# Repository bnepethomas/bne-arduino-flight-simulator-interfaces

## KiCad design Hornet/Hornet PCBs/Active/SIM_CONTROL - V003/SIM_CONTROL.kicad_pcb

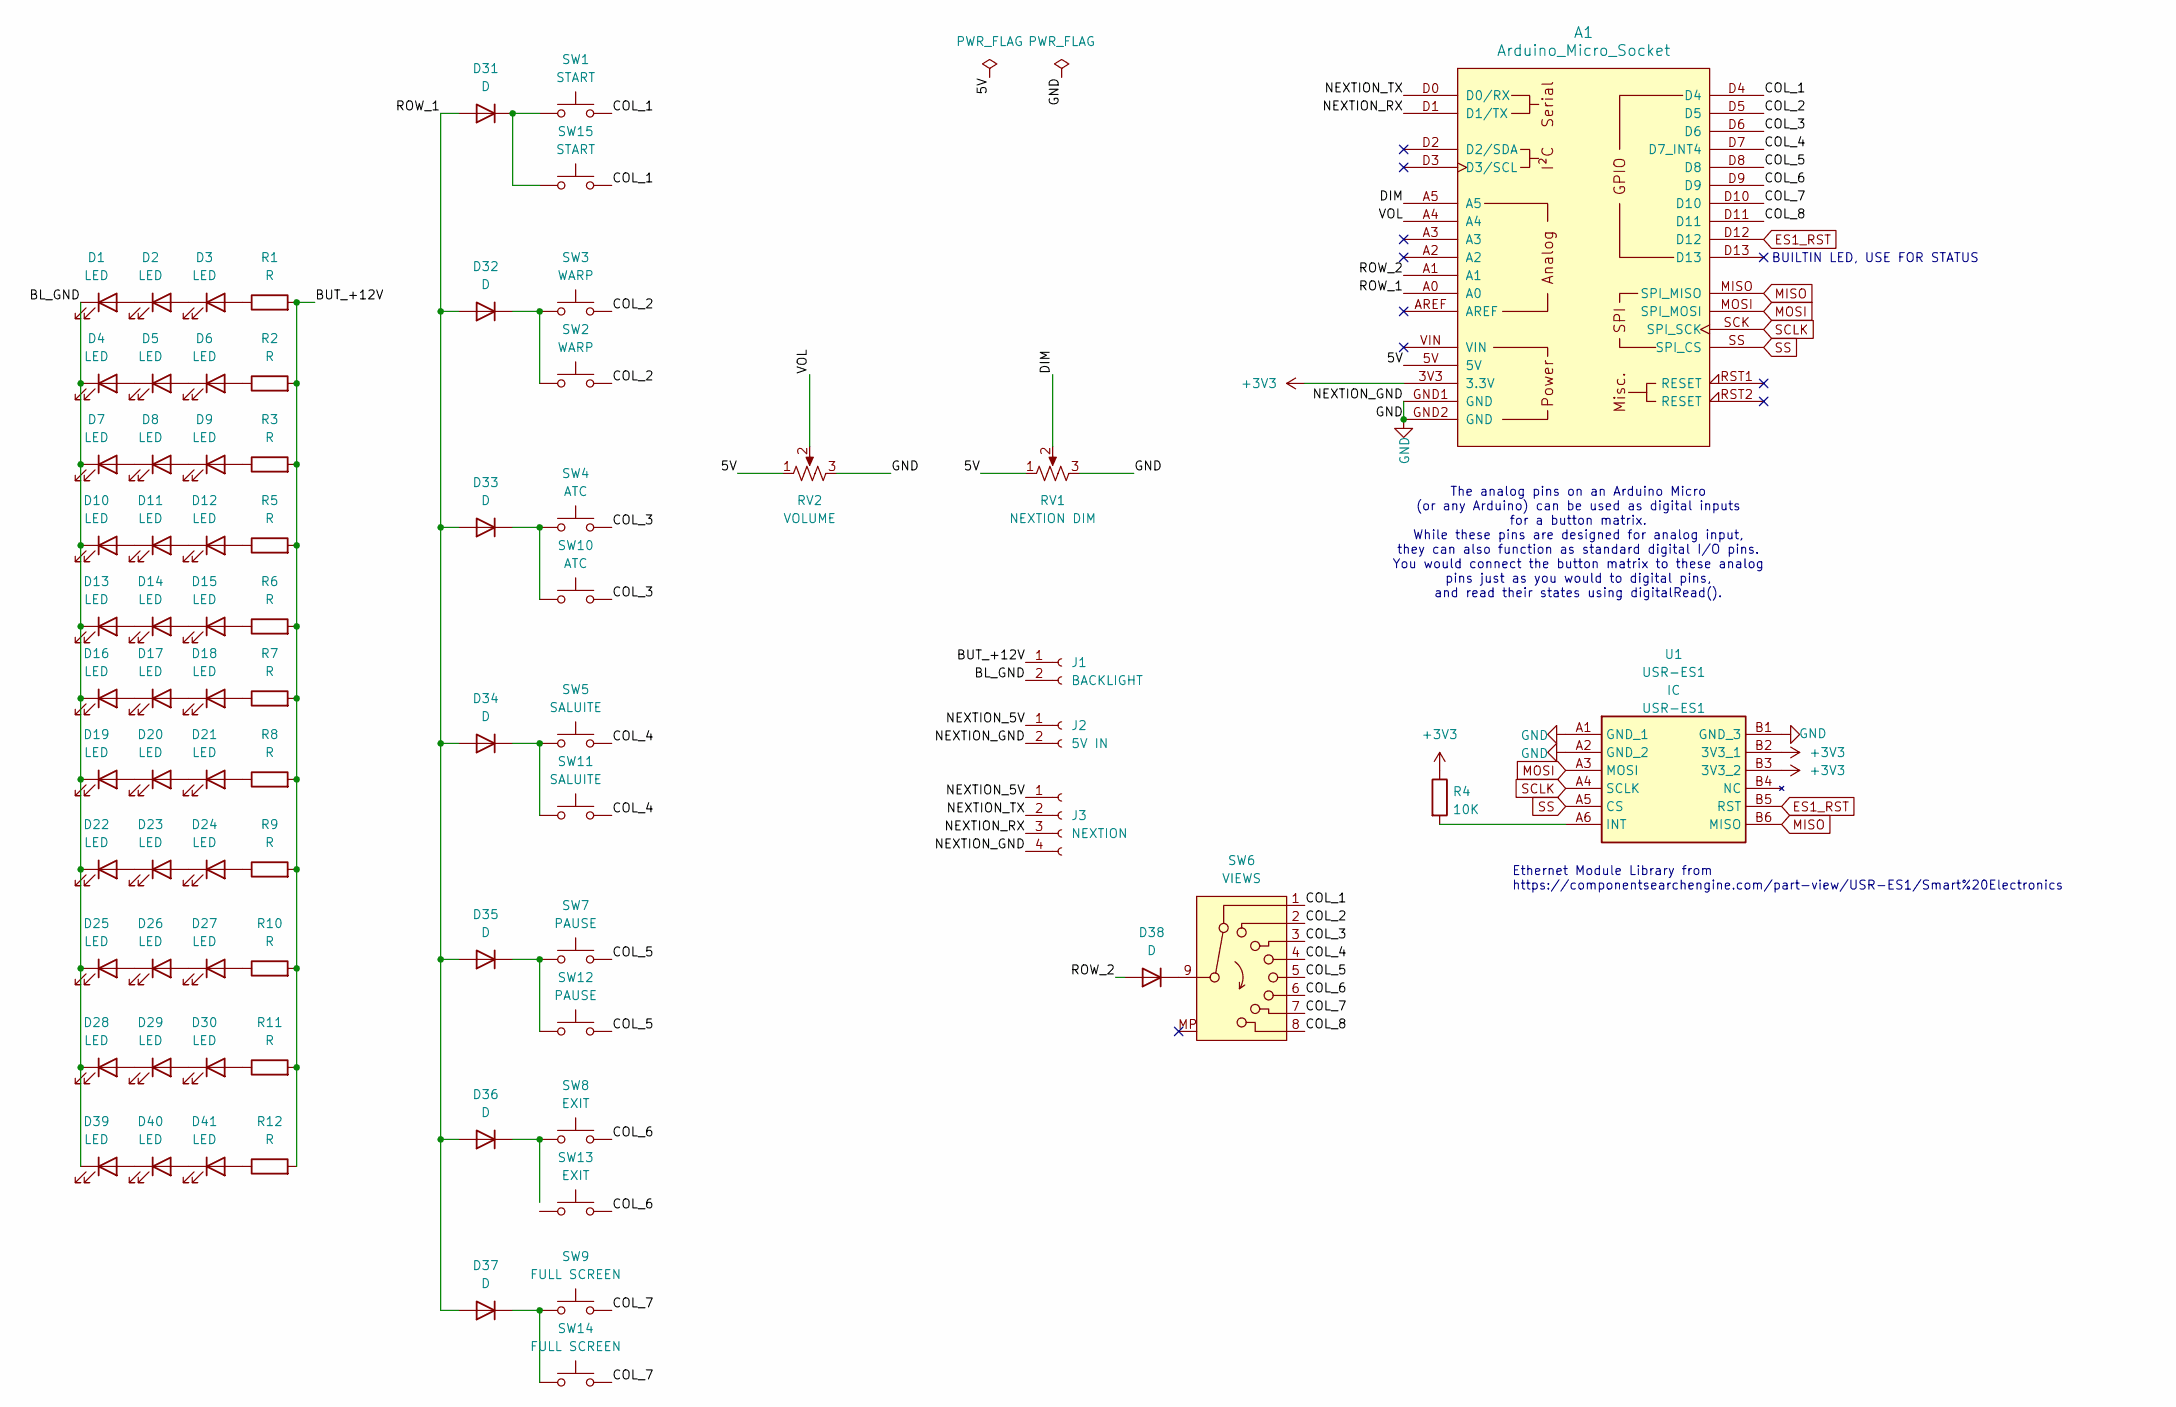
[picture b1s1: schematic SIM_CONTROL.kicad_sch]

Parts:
A1: Arduino_Micro_Socket
D1, D2, D3, D4, D5, D6, D7, D8, D9, D10, D11, D12, D13, D14, D15, D16, D17, D18, D19, D20, D21, D22, D23, D24, D25, D26, D27, D28, D29, D30, D39, D40, D41: LED; LED_0805_2012Metric
D31, D32, D33, D34, D35, D36, D37, D38: D; D_0805_2012Metric_Pad1.15x1.40mm_HandSolder
J1: BACKLIGHT; Molex_KK-254_AE-6410-02A_1x02_P2.54mm_Vertical
J2: 5V IN; BarrelJack_Horizontal
J3: NEXTION; Molex_KK-254_AE-6410-04A_1x04_P2.54mm_Vertical
R1, R2, R3, R5, R6, R7, R8, R9, R10, R11, R12: R; R_0805_2012Metric
R4: 10K; R_0805_2012Metric
RV1: NEXTION DIM; JST_XA_B03B-XASK-1_1x03_P2.50mm_Vertical
RV2: VOLUME; JST_XA_B03B-XASK-1_1x03_P2.50mm_Vertical
SW1, SW15: START; SW_Push_1P1T_XKB_TS-1187A
SW2, SW3: WARP; SW_Push_1P1T_XKB_TS-1187A
SW4, SW10: ATC; SW_Push_1P1T_XKB_TS-1187A
SW5, SW11: SALUITE; SW_Push_1P1T_XKB_TS-1187A
SW6: VIEWS; Molex_KK-254_AE-6410-10A_1x10_P2.54mm_Vertical
SW7, SW12: PAUSE; SW_Push_1P1T_XKB_TS-1187A
SW8, SW13: EXIT; SW_Push_1P1T_XKB_TS-1187A
SW9, SW14: FULL SCREEN; SW_Push_1P1T_XKB_TS-1187A
U1: USR-ES1; USRES1; Manufacturer_Part_Number USR-ES1

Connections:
+3V3: A1.3V3 (3.3V), R4.1, U1.B2 (3V3_1), U1.B3 (3V3_2)
/5V: A1.5V, RV1.1, RV2.1
/BL_GND: D1.1 (K), D4.1 (K), D7.1 (K), D10.1 (K), D13.1 (K), D16.1 (K), D19.1 (K), D22.1 (K), D25.1 (K), D28.1 (K), D39.1 (K), J1.2
/BUT_+12V: J1.1, R1.2, R2.2, R3.2, R5.2, R6.2, R7.2, R8.2, R9.2, R10.2, R11.2, R12.2
/COL_1: A1.D4, SW1.2, SW6.1, SW15.2
/COL_2: A1.D5, SW2.2, SW3.2, SW6.2
/COL_3: A1.D6, SW4.2, SW6.3, SW10.2
/COL_4: A1.D7 (D7_INT4), SW5.2, SW6.4, SW11.2
/COL_5: A1.D8, SW6.5, SW7.2, SW12.2
/COL_6: A1.D9, SW6.6, SW8.2, SW13.2
/COL_7: A1.D10, SW6.7, SW9.2, SW14.2
/COL_8: A1.D11, SW6.8
/DIM: A1.A5, RV1.2
/NEXTION_5V: J2.1, J3.1
/NEXTION_RX: A1.D1 (D1/TX), J3.3
/NEXTION_TX: A1.D0 (D0/RX), J3.2
/ROW_1: A1.A0, D31.2 (A), D32.2 (A), D33.2 (A), D34.2 (A), D35.2 (A), D36.2 (A), D37.2 (A)
/ROW_2: A1.A1, D38.2 (A)
/VOL: A1.A4, RV2.2
ES1_RST: A1.D12, U1.B5 (RST)
GND: A1.GND1 (GND), A1.GND2 (GND), J2.2, J3.4, RV1.3, RV2.3, U1.A1 (GND_1), U1.A2 (GND_2), U1.B1 (GND_3)
MISO: A1.MISO (SPI_MISO), U1.B6 (MISO)
MOSI: A1.MOSI (SPI_MOSI), U1.A3 (MOSI)
unnamed: D1.2 (A), D2.1 (K)
unnamed: D2.2 (A), D3.1 (K)
unnamed: D3.2 (A), R1.1
unnamed: D4.2 (A), D5.1 (K)
unnamed: D5.2 (A), D6.1 (K)
unnamed: D6.2 (A), R2.1
unnamed: D7.2 (A), D8.1 (K)
unnamed: D8.2 (A), D9.1 (K)
unnamed: D9.2 (A), R3.1
unnamed: D10.2 (A), D11.1 (K)
unnamed: D11.2 (A), D12.1 (K)
unnamed: D12.2 (A), R5.1
unnamed: D13.2 (A), D14.1 (K)
unnamed: D14.2 (A), D15.1 (K)
unnamed: D15.2 (A), R6.1
unnamed: D16.2 (A), D17.1 (K)
unnamed: D17.2 (A), D18.1 (K)
unnamed: D18.2 (A), R7.1
unnamed: D19.2 (A), D20.1 (K)
unnamed: D20.2 (A), D21.1 (K)
unnamed: D21.2 (A), R8.1
unnamed: D22.2 (A), D23.1 (K)
unnamed: D23.2 (A), D24.1 (K)
unnamed: D24.2 (A), R9.1
unnamed: D25.2 (A), D26.1 (K)
unnamed: D26.2 (A), D27.1 (K)
unnamed: D27.2 (A), R10.1
unnamed: D28.2 (A), D29.1 (K)
unnamed: D29.2 (A), D30.1 (K)
unnamed: D30.2 (A), R11.1
unnamed: D31.1 (K), SW1.1, SW15.1
unnamed: D32.1 (K), SW2.1, SW3.1
unnamed: D33.1 (K), SW4.1, SW10.1
unnamed: D34.1 (K), SW5.1, SW11.1
unnamed: D35.1 (K), SW7.1, SW12.1
unnamed: D36.1 (K), SW8.1
unnamed: D37.1 (K), SW9.1, SW14.1
unnamed: D38.1 (K), SW6.9
unnamed: D39.2 (A), D40.1 (K)
unnamed: D40.2 (A), D41.1 (K)
unnamed: D41.2 (A), R12.1
unnamed: R4.2, U1.A6 (INT)
SCLK: A1.SCK (SPI_SCK), U1.A4 (SCLK)
SS: A1.SS (SPI_CS), U1.A5 (CS)

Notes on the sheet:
Ethernet Module Library from https://componentsearchengine.com/part-view/USR-ES1/Smart%20Electronics
The analog pins on an Arduino Micro (or any Arduino) can be used as digital inputs for a button matrix. While these pins are designed for analog input, they can also function as standard digital I/O pins. You would connect the button matrix to these analog pins just as you would to digital pins, an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
BUILTIN LED, USE FOR STATUS

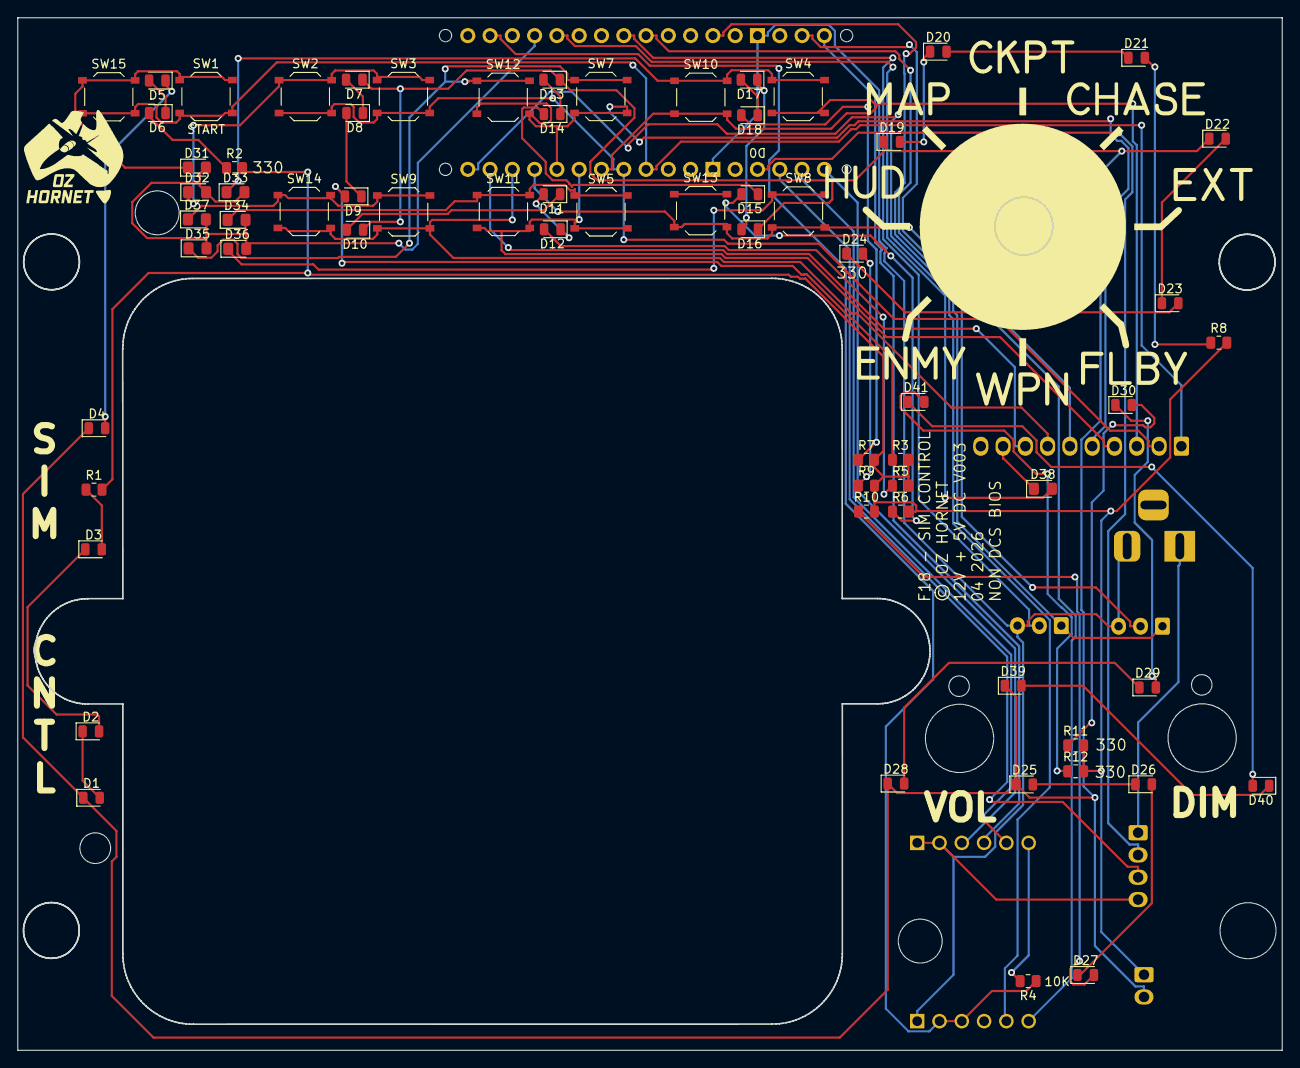
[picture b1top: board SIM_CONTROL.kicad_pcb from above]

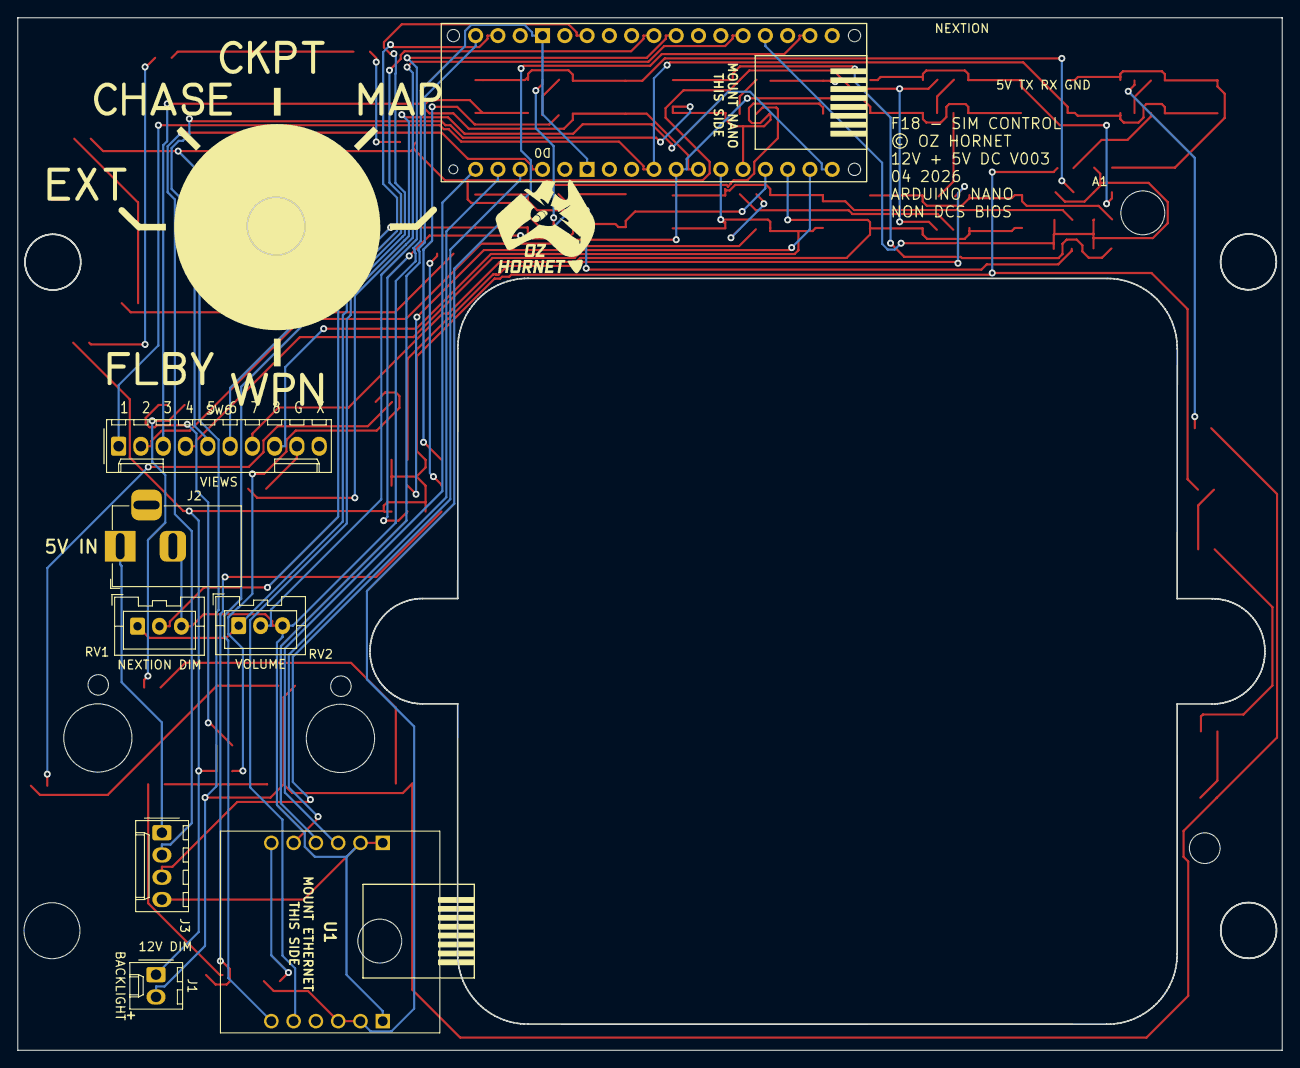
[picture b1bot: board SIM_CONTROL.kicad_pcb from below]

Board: 2 copper layers, 144.1 x 117.7 mm, 76 parts (8 on the bottom side), 67 nets.

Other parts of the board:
MH12: Switch_Rotary_8pos45Deg; A12505RNZQ - SWITCH, ROTARY, 45 DEG, 8-POS

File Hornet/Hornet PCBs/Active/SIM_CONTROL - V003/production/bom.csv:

Designator,Footprint,Quantity,Value,LCSC Part #
A1,Arduino_Micro_Socket,1,Arduino_Micro_Socket,
"D1, D10, D11, D12, D13, D14, D15, D16, D17, D18, D19, D2, D20, D21, D22, D23, D24, D25, D26, D27, D28, D29, D3, D30, D39, D4, D40, D41, D5, D6, D7, D8, D9",0805,33,LED,
"D31, D32, D33, D34, D35, D36, D37, D38",0805,8,D,
J1,Molex_KK-254_AE-6410-02A_1x02_P2.54mm_Vertical,1,BACKLIGHT,
J2,BarrelJack_Horizontal,1,5V IN,
J3,Molex_KK-254_AE-6410-04A_1x04_P2.54mm_Vertical,1,NEXTION,
"R1, R10, R11, R12, R2, R3, R5, R6, R7, R8, R9",0805,11,R,
R4,0805,1,10K,
RV1,JST_XA_B03B-XASK-1_1x03_P2.50mm_Vertical,1,NEXTION DIM,
RV2,JST_XA_B03B-XASK-1_1x03_P2.50mm_Vertical,1,VOLUME,
"SW1, SW15",SW_Push_1P1T_XKB_TS-1187A,2,START,
"SW10, SW4",SW_Push_1P1T_XKB_TS-1187A,2,ATC,
"SW11, SW5",SW_Push_1P1T_XKB_TS-1187A,2,SALUITE,
"SW12, SW7",SW_Push_1P1T_XKB_TS-1187A,2,PAUSE,
"SW13, SW8",SW_Push_1P1T_XKB_TS-1187A,2,EXIT,
"SW14, SW9",SW_Push_1P1T_XKB_TS-1187A,2,FULL SCREEN,
"SW2, SW3",SW_Push_1P1T_XKB_TS-1187A,2,WARP,
SW6,Molex_KK-254_AE-6410-10A_1x10_P2.54mm_Vertical,1,VIEWS,
U1,USRES1,1,USR-ES1,

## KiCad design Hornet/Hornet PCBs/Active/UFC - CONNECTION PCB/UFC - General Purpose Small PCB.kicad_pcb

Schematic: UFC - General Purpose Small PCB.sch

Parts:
D1: LED; LED_D5.0mm
H1, H2, H3, H4, H5, H6, H7, H8, H9: MountingHole; MountingHole_3.2mm_M3
J1: AP COL IN; Molex_1x03_P2.54mm_Vertical
J2: AP ROW IN; Molex_1x03_P2.54mm_Vertical
J3: AP COL OUT; Molex_1x03_P2.54mm_Vertical
J4: AP ROW OUT; Molex_1x03_P2.54mm_Vertical
J5: UFC LED COL IN; Molex_1x03_P2.54mm_Vertical
J6: UFC LED ROW IN; Molex_1x04_P2.54mm_Vertical
J7: UFC ROW IN; Molex_1x06_P2.54mm_Vertical
J8: UFC COL IN; Molex_1x04_P2.54mm_Vertical
J9: UFC R ENC IN; Molex_1x06_P2.54mm_Vertical
J10: UFC L ENC IN; Molex_1x06_P2.54mm_Vertical
J11: UFC ANALOG IN; Molex_1x06_P2.54mm_Vertical
J12: BACKLIGHT IN; Molex_1x02_P2.54mm_Vertical
J13: UFC LED COL OUT; Molex_1x03_P2.54mm_Vertical
J14: UFC LED ROW OUT; Molex_1x04_P2.54mm_Vertical
J15: UFC ROW OUT; Molex_1x06_P2.54mm_Vertical
J16: UFC COL OUT; Molex_1x04_P2.54mm_Vertical
J17: UFC R ENC OUT; Molex_1x06_P2.54mm_Vertical
J18: UFC L ENC OUT; Molex_1x06_P2.54mm_Vertical
J19: UFC ANALOG OUT; Molex_1x06_P2.54mm_Vertical
J20: UFC BL OUT; Molex_1x02_P2.54mm_Vertical
J21: AP BL OUT; Molex_1x02_P2.54mm_Vertical
J22: SPARE BL OUT; Molex_1x02_P2.54mm_Vertical
J23: POWER SELECT; PinHeader_1x03_P2.54mm_Vertical
J24: 5V POWER IN; BarrelJack_Horizontal
J25: PIXEL LED OUT 4; Molex_1x03_P2.54mm_Vertical
J26: PIXEL LED OUT 1; Molex_1x03_P2.54mm_Vertical
J27: PIXEL LED OUT 2; Molex_1x03_P2.54mm_Vertical
J28: PIXEL LED OUT 3; Molex_1x03_P2.54mm_Vertical
J29: PIXEL LED IN; Molex_1x06_P2.54mm_Vertical
J30: PIXEL LED OUT 1; Molex_Mini-Fit_Jr_5566-04A_2x02_P4.20mm_Vertical
J31: PIXEL LED OUT 2; Molex_Mini-Fit_Jr_5566-04A_2x02_P4.20mm_Vertical
J32: PIXEL LED OUT 3; Molex_Mini-Fit_Jr_5566-04A_2x02_P4.20mm_Vertical
J33: PIXEL LED OUT 4; Molex_Mini-Fit_Jr_5566-04A_2x02_P4.20mm_Vertical
R1: 1K; R_Axial_DIN0207_L6.3mm_D2.5mm_P7.62mm_Horizontal

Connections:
/ARDUINO_5V: J23.1, J29.1
/BACKLIGHT_+12V: J12.1, J20.1, J21.1, J22.1
/BACKLIGHT_GND: J12.2, J20.2, J21.2, J22.2
/PIXEL_LED_5V: J23.2, J25.1, J26.1, J27.1, J28.1, J30.1, J30.2, J31.1, J31.2, J32.1, J32.2, J33.1, J33.2, R1.1
/PIXEL_LED_GND: D1.1, J24.2, J25.2, J26.2, J27.2, J28.2, J29.2, J30.3, J31.3, J32.3, J33.3
/PIXEL_LED_IN_1: J26.3, J29.3, J30.4, J31.4
/PIXEL_LED_IN_2: J27.3, J29.4
/PIXEL_LED_IN_3: J28.3, J29.5, J32.4
/PIXEL_LED_IN_4: J25.3, J29.6, J33.4
/RAW_5V: J23.3, J24.1
unnamed: D1.2, R1.2
unnamed: J1.1, J3.1
unnamed: J1.2, J3.2
unnamed: J1.3, J3.3
unnamed: J2.1, J4.1
unnamed: J2.2, J4.2
unnamed: J2.3, J4.3
unnamed: J10.1, J18.1
unnamed: J10.2, J18.2
unnamed: J10.3, J18.3
unnamed: J10.4, J18.4
unnamed: J10.5, J18.5
unnamed: J10.6, J18.6
unnamed: J11.1, J19.1
unnamed: J11.2, J19.2
unnamed: J11.3, J19.3
unnamed: J11.4, J19.4
unnamed: J11.5, J19.5
unnamed: J11.6, J19.6
unnamed: J5.1, J13.1
unnamed: J5.2, J13.2
unnamed: J5.3, J13.3
unnamed: J6.1, J14.1
unnamed: J6.2, J14.2
unnamed: J6.3, J14.3
unnamed: J6.4, J14.4
unnamed: J7.1, J15.1
unnamed: J7.2, J15.2
unnamed: J7.3, J15.3
unnamed: J7.4, J15.4
unnamed: J7.5, J15.5
unnamed: J7.6, J15.6
unnamed: J8.1, J16.1
unnamed: J8.2, J16.2
unnamed: J8.3, J16.3
unnamed: J8.4, J16.4
unnamed: J9.1, J17.1
unnamed: J9.2, J17.2
unnamed: J9.3, J17.3
unnamed: J9.4, J17.4
unnamed: J9.5, J17.5
unnamed: J9.6, J17.6

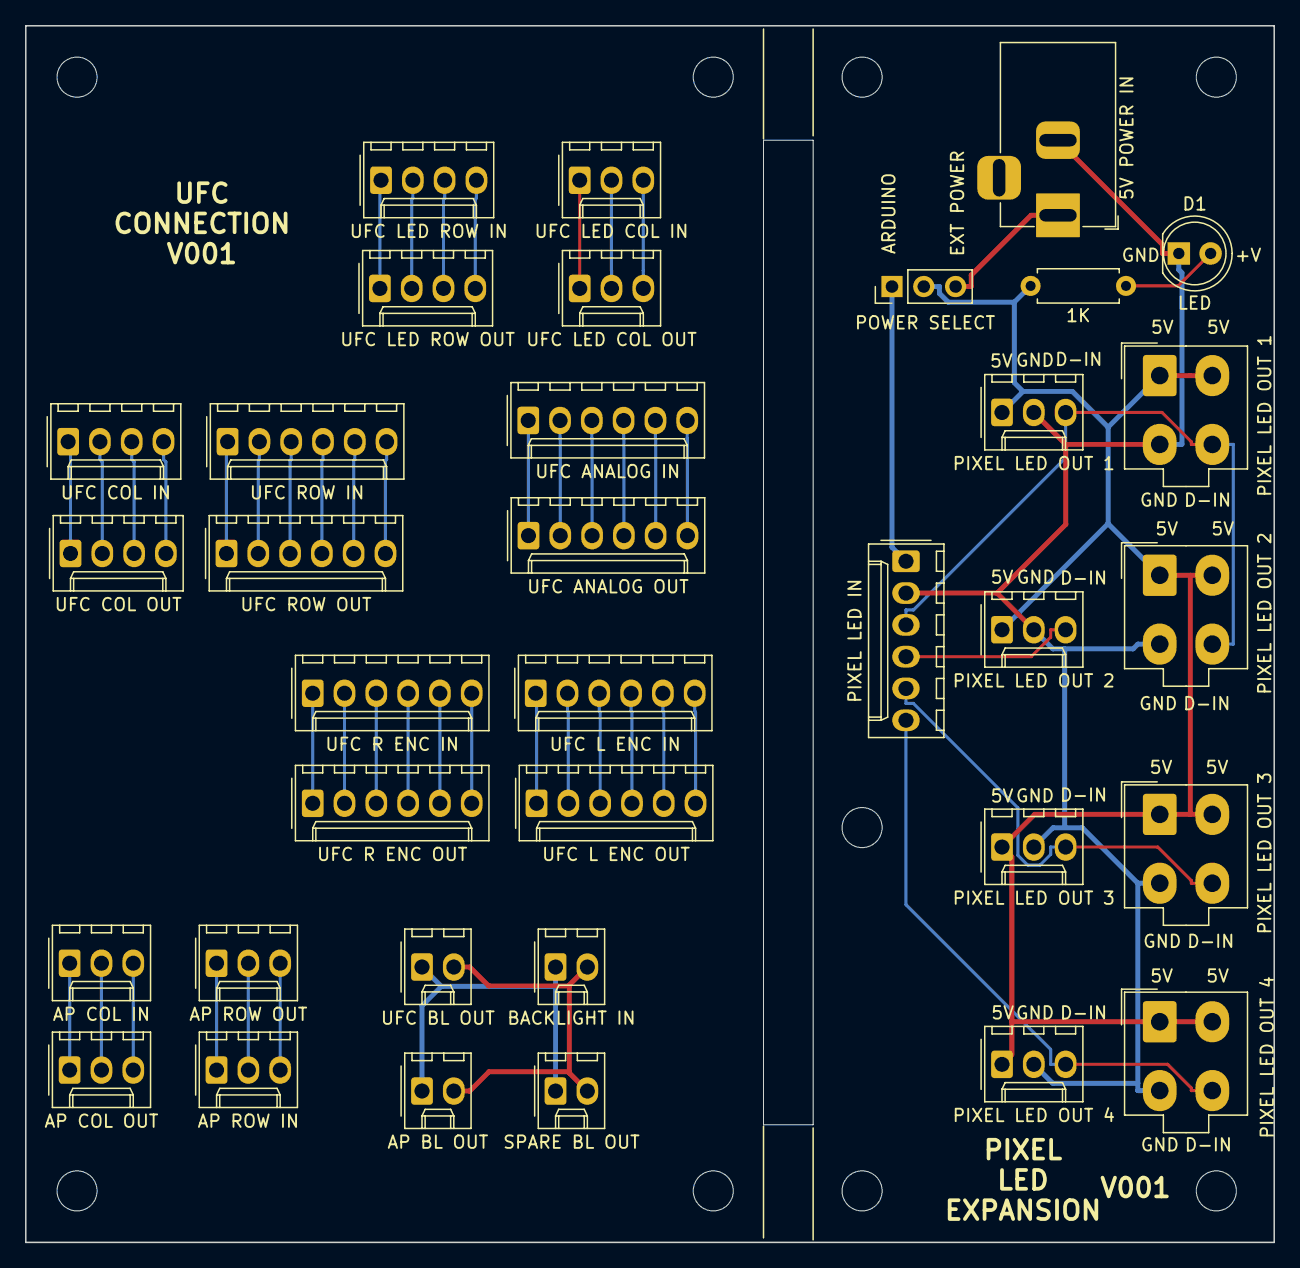
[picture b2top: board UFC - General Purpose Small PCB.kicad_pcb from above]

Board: 2 copper layers, 99.7 x 97.2 mm, 44 parts (0 on the bottom side), 52 nets.

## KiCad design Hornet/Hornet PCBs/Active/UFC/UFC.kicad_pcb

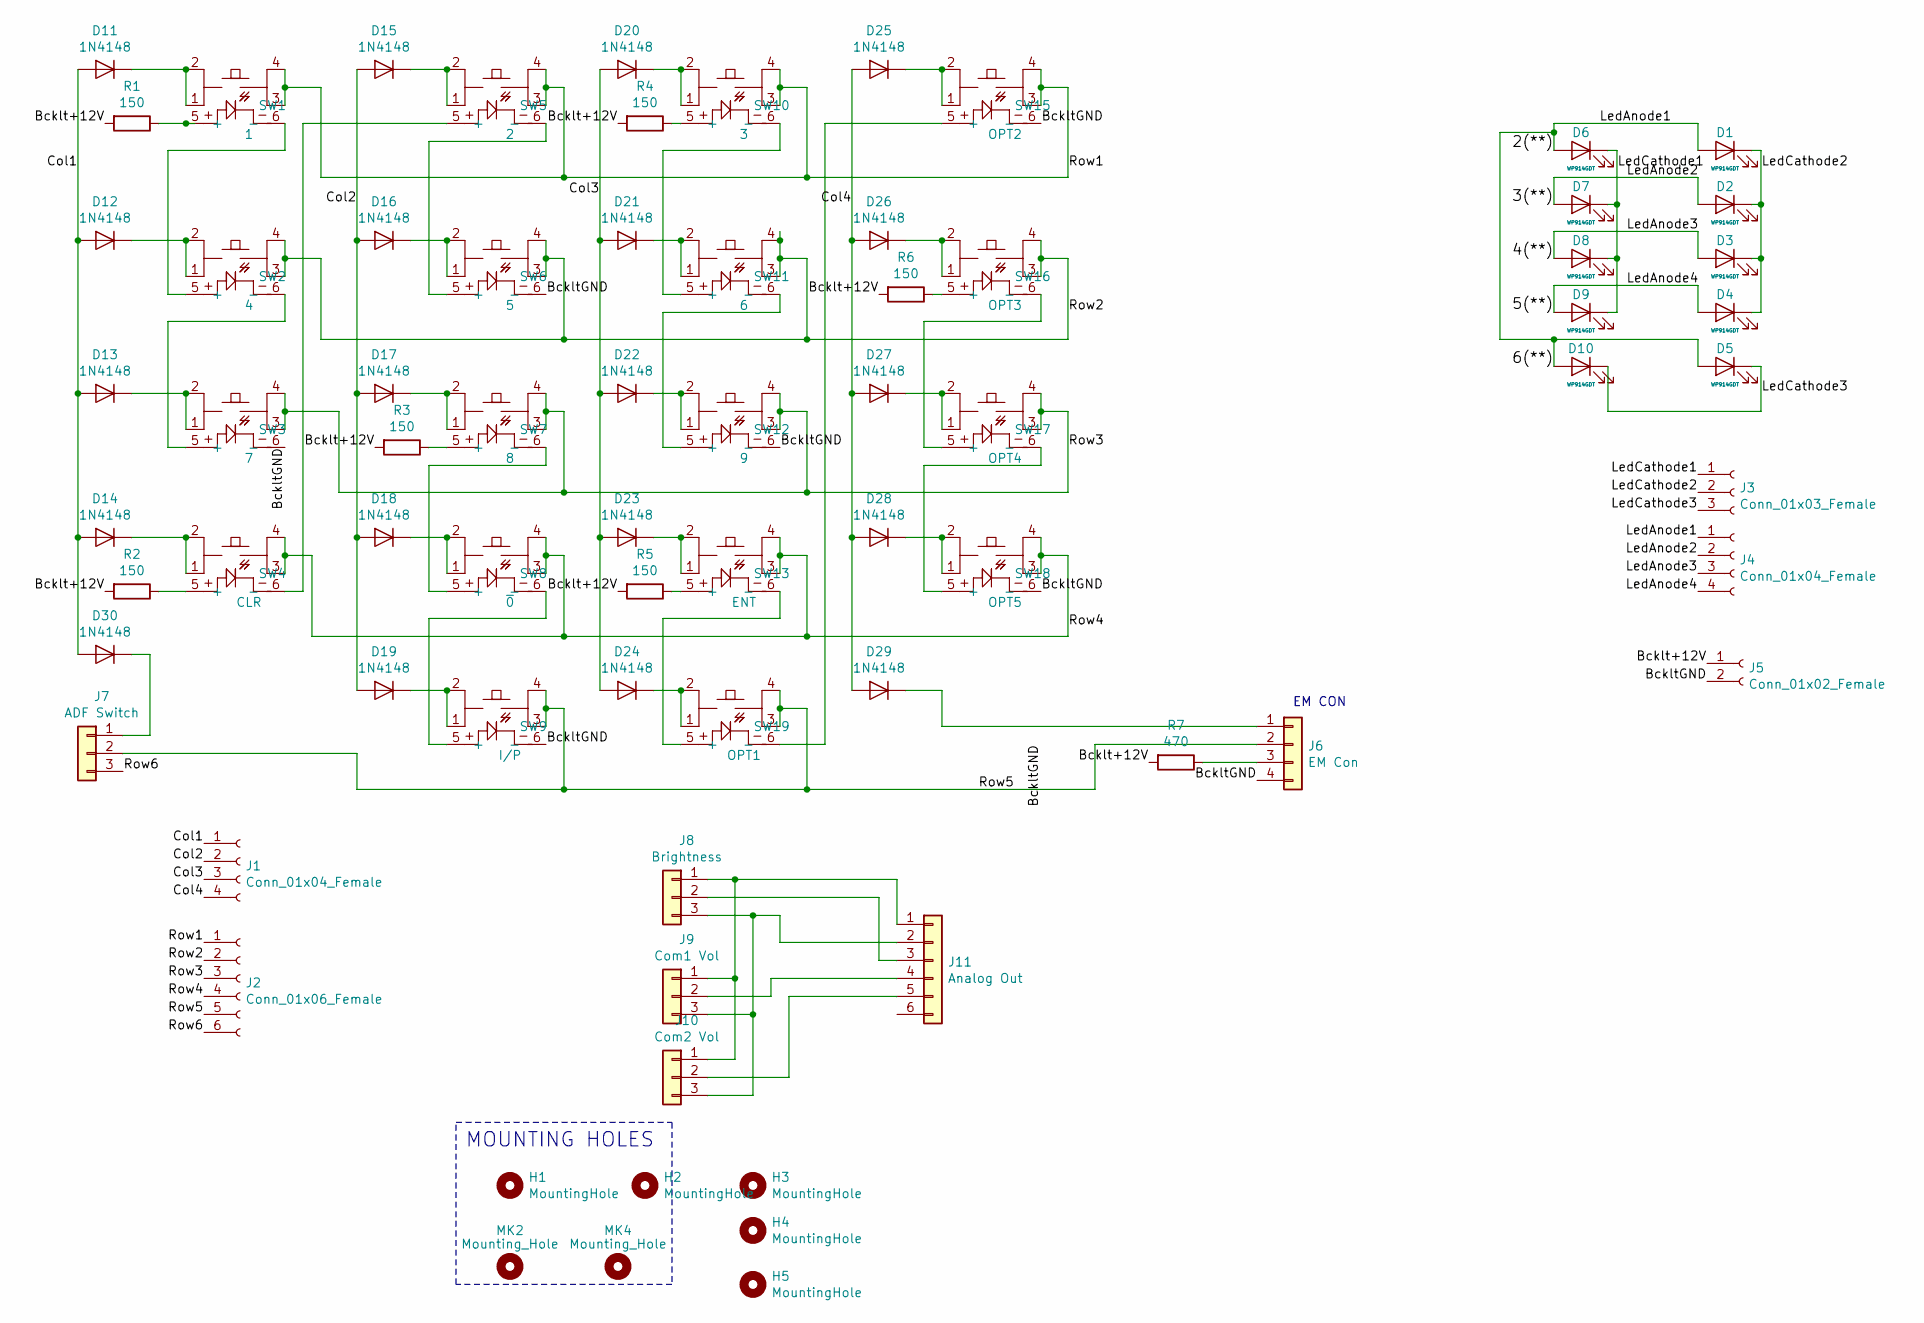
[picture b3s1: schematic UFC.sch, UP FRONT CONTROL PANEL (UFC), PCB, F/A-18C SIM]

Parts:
D1, D2, D3, D4, D5, D6, D7, D8, D9, D10: WP914GDT; LED_D3.0mm
D11, D12, D13, D14, D15, D16, D17, D18, D19, D20, D21, D22, D23, D24, D25, D26, D27, D28, D29, D30: 1N4148; D_DO-35_SOD27_P7.62mm_Horizontal
H1, H2, H3, H4, H5: MountingHole; MountingHole_3.2mm_M3
J1, J4: Conn_01x04_Female; Molex_1x04_P2.54mm_Vertical
J2: Conn_01x06_Female; Molex_1x06_P2.54mm_Vertical
J3: Conn_01x03_Female; Molex_1x03_P2.54mm_Vertical
J5: Conn_01x02_Female; Molex_1x02_P2.54mm_Vertical
J6: EM Con; Molex_1x04_P2.54mm_Vertical
J7: ADF Switch; Molex_1x03_P2.54mm_Vertical
J8: Brightness; Molex_1x03_P2.54mm_Vertical
J9: Com1 Vol; Molex_1x03_P2.54mm_Vertical
J10: Com2 Vol; Molex_1x03_P2.54mm_Vertical
J11: Analog Out; Molex_1x06_P2.54mm_Vertical
MK2, MK4: Mounting_Hole; MountingHole_3mm
R1, R2, R3, R4, R5, R6: 150; R_Axial_DIN0207_L6.3mm_D2.5mm_P7.62mm_Horizontal
R7: 470; R_Axial_DIN0207_L6.3mm_D2.5mm_P7.62mm_Horizontal
SW1: 1; PT_Small_Tactile_Switch_With_LED
SW2: 4; PT_Small_Tactile_Switch_With_LED
SW3: 7; PT_Small_Tactile_Switch_With_LED
SW4: CLR; PT_Small_Tactile_Switch_With_LED
SW5: 2; PT_Small_Tactile_Switch_With_LED
SW6: 5; PT_Small_Tactile_Switch_With_LED
SW7: 8; PT_Small_Tactile_Switch_With_LED
SW8: ~0; PT_Small_Tactile_Switch_With_LED
SW9: I/P; PT_Small_Tactile_Switch_With_LED
SW10: 3; PT_Small_Tactile_Switch_With_LED
SW11: 6; PT_Small_Tactile_Switch_With_LED
SW12: 9; PT_Small_Tactile_Switch_With_LED
SW13: ENT; PT_Small_Tactile_Switch_With_LED
SW15: OPT2; PT_Small_Tactile_Switch_With_LED
SW16: OPT3; PT_Small_Tactile_Switch_With_LED
SW17: OPT4; PT_Small_Tactile_Switch_With_LED
SW18: OPT5; PT_Small_Tactile_Switch_With_LED
SW19: OPT1; PT_Small_Tactile_Switch_With_LED

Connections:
/2(**): D1.2 (A), D5.2 (A), D6.2 (A), D10.2 (A), J4.1
/3(**): D2.2 (A), D7.2 (A), J4.2
/4(**): D3.2 (A), D8.2 (A), J4.3
/5(**): D4.2 (A), D9.2 (A), J4.4
/Bcklt+12V: J5.1, R1.2, R2.2, R3.2, R4.2, R5.2, R6.2, R7.2
/BckltGND: J5.2, J6.4, SW3.6 (-), SW6.6 (-), SW9.6 (-), SW12.6 (-), SW15.6 (-), SW18.6 (-)
/Col1: D11.2 (A), D12.2 (A), D13.2 (A), D14.2 (A), D30.2 (A), J1.1
/Col2: D15.2 (A), D16.2 (A), D17.2 (A), D18.2 (A), D19.2 (A), J1.2
/Col3: D20.2 (A), D21.2 (A), D22.2 (A), D23.2 (A), D24.2 (A), J1.3
/Col4: D25.2 (A), D26.2 (A), D27.2 (A), D28.2 (A), D29.2 (A), J1.4
/LedCathode1: D6.1 (K), D7.1 (K), D8.1 (K), D9.1 (K), J3.1
/LedCathode2: D1.1 (K), D2.1 (K), D3.1 (K), D4.1 (K), J3.2
/LedCathode3: D5.1 (K), D10.1 (K), J3.3
/Row1: J2.1, SW1.3, SW1.4, SW5.3, SW5.4, SW10.3, SW10.4, SW15.3, SW15.4
/Row2: J2.2, SW2.3, SW2.4, SW6.3, SW6.4, SW11.3, SW11.4, SW16.3, SW16.4
/Row3: J2.3, SW3.3, SW3.4, SW7.3, SW7.4, SW12.3, SW12.4, SW17.3, SW17.4
/Row4: J2.4, SW4.3, SW4.4, SW8.3, SW8.4, SW13.3, SW13.4, SW18.3, SW18.4
/Row5: J2.5, J6.2, J7.2, SW9.3, SW9.4, SW19.3, SW19.4
/Row6: J2.6, J7.3
unnamed: D11.1 (K), SW1.1, SW1.2
unnamed: D12.1 (K), SW2.1, SW2.2
unnamed: D13.1 (K), SW3.1, SW3.2
unnamed: D14.1 (K), SW4.1, SW4.2
unnamed: D15.1 (K), SW5.1, SW5.2
unnamed: D16.1 (K), SW6.1, SW6.2
unnamed: D17.1 (K), SW7.1, SW7.2
unnamed: D18.1 (K), SW8.1, SW8.2
unnamed: D19.1 (K), SW9.1, SW9.2
unnamed: D20.1 (K), SW10.1, SW10.2
unnamed: D21.1 (K), SW11.1, SW11.2
unnamed: D22.1 (K), SW12.1, SW12.2
unnamed: D23.1 (K), SW13.1, SW13.2
unnamed: D24.1 (K), SW19.1, SW19.2
unnamed: D25.1 (K), SW15.1, SW15.2
unnamed: D26.1 (K), SW16.1, SW16.2
unnamed: D27.1 (K), SW17.1, SW17.2
unnamed: D28.1 (K), SW18.1, SW18.2
unnamed: D29.1 (K), J6.1
unnamed: D30.1 (K), J7.1
unnamed: J6.3, R7.1
unnamed: J8.1, J9.1, J10.1, J11.1
unnamed: J10.2, J11.5
unnamed: J8.3, J9.3, J10.3, J11.2
unnamed: J8.2, J11.3
unnamed: J9.2, J11.4
unnamed: R1.1, SW1.5 (+)
unnamed: R2.1, SW4.5 (+)
unnamed: R3.1, SW7.5 (+)
unnamed: R4.1, SW10.5 (+)
unnamed: R5.1, SW13.5 (+)
unnamed: R6.1, SW16.5 (+)
unnamed: SW1.6 (-), SW2.5 (+)
unnamed: SW2.6 (-), SW3.5 (+)
unnamed: SW4.6 (-), SW5.5 (+)
unnamed: SW5.6 (-), SW6.5 (+)
unnamed: SW7.6 (-), SW8.5 (+)
unnamed: SW8.6 (-), SW9.5 (+)
unnamed: SW10.6 (-), SW11.5 (+)
unnamed: SW11.6 (-), SW12.5 (+)
unnamed: SW13.6 (-), SW19.5 (+)
unnamed: SW15.5 (+), SW19.6 (-)
unnamed: SW16.6 (-), SW17.5 (+)
unnamed: SW17.6 (-), SW18.5 (+)

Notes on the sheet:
MOUNTING HOLES
EM CON

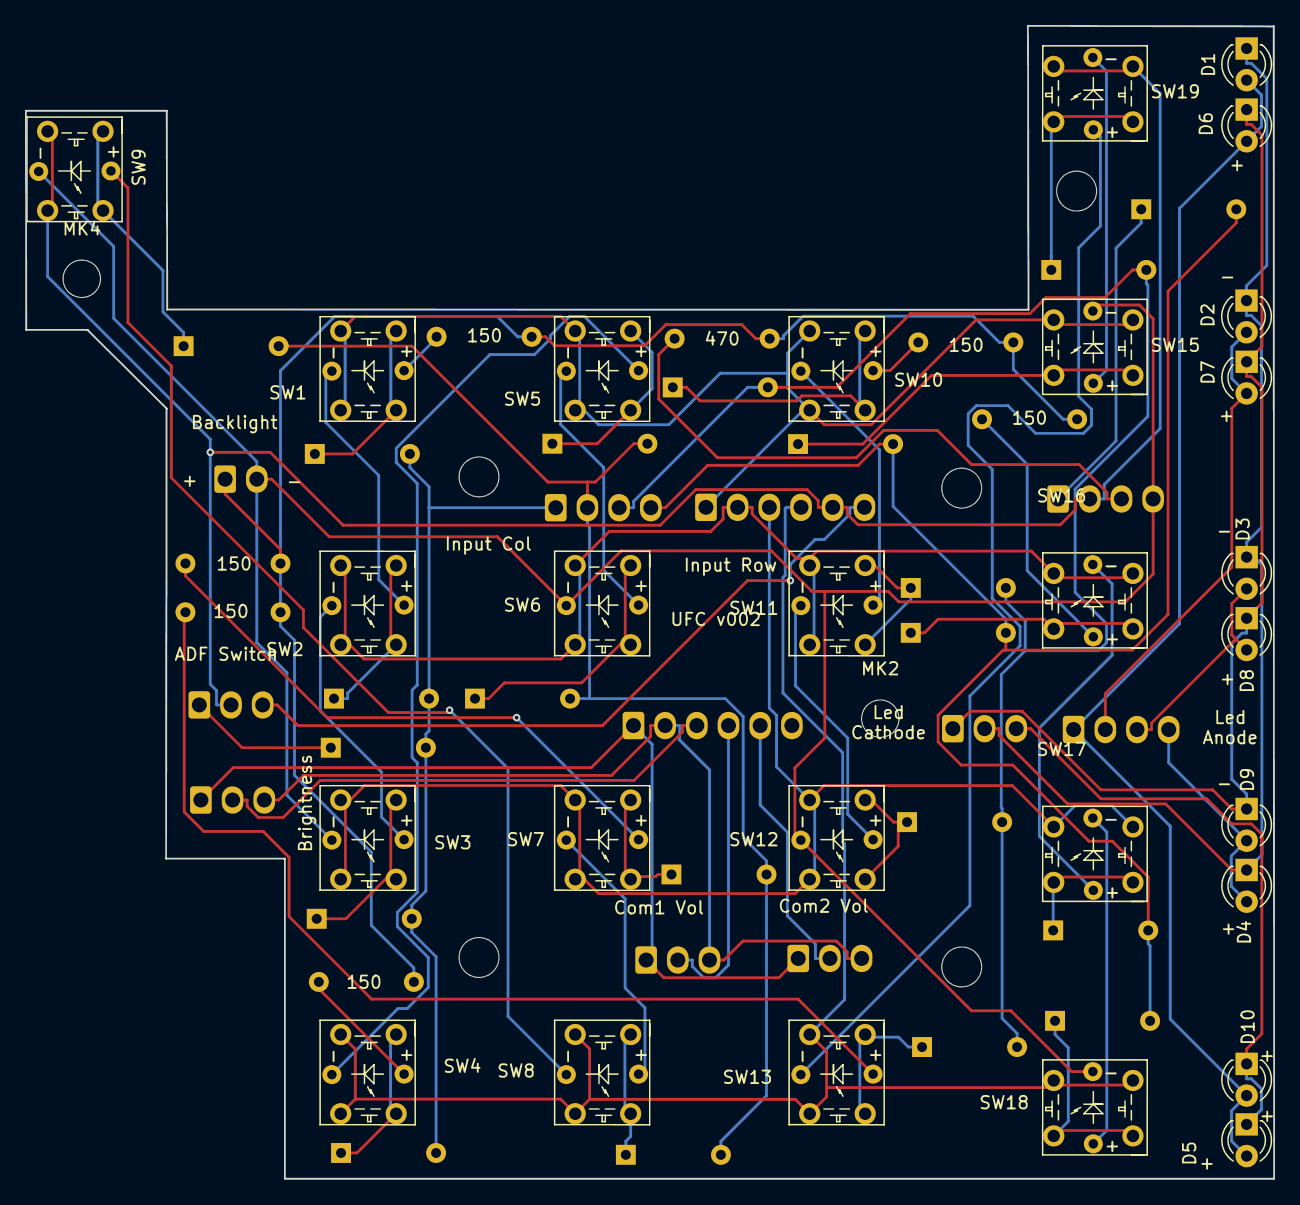
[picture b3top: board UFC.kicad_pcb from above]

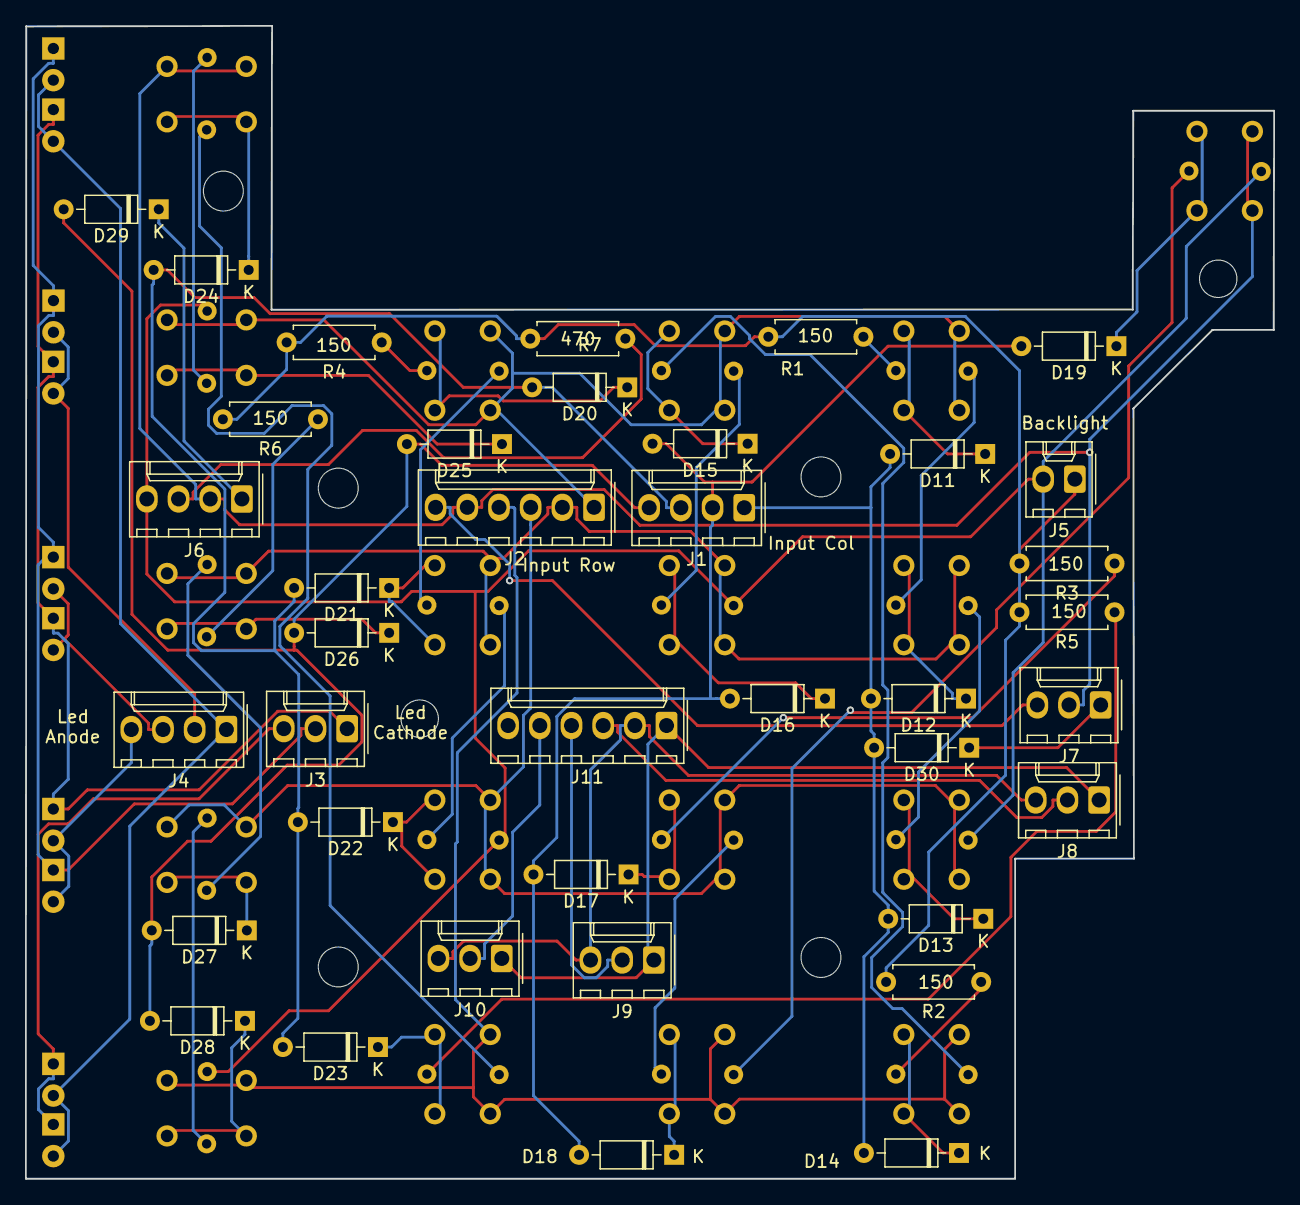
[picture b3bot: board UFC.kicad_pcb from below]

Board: 2 copper layers, 100.0 x 92.4 mm, 73 parts (38 on the bottom side), 63 nets.

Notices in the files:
Hornet/Hornet PCBs/Active/SIM_CONTROL - V003/SIM_CONTROL.kicad_pcb:
© OZ HORNET
